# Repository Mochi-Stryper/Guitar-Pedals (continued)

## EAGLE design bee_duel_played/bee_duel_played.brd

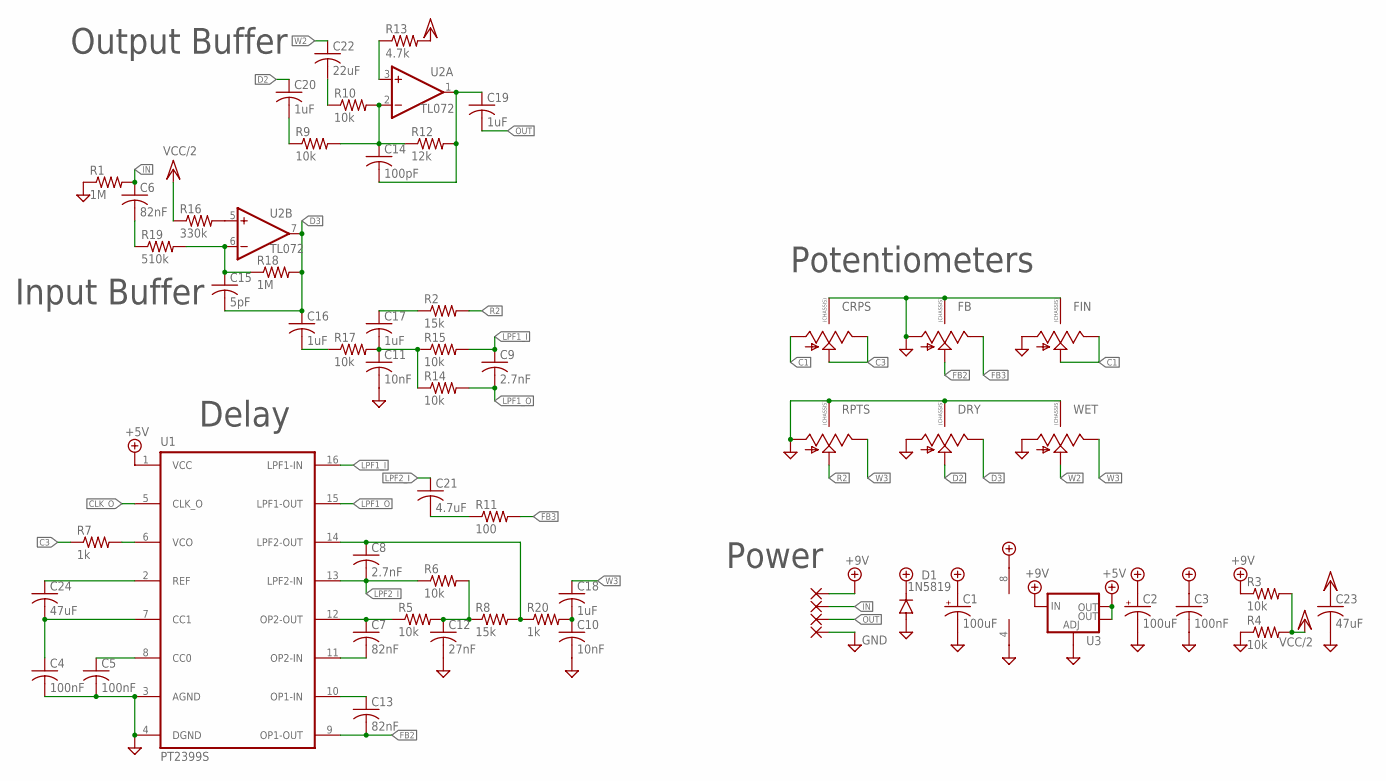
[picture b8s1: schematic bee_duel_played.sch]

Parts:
C1, C2: 100uF; CPOL-RADIAL-2.5MM-6.5MM
C3, C4, C5: 100nF; C0603
C6, C7, C13: 82nF; C0603
C8, C9: 2.7nF; C0603
C10, C11: 10nF; C0603
C12: 27nF; C0603
C14: 100pF; C0603
C15: 5pF; C0603
C16, C17, C18, C19, C20: 1uF; C0603
C21: 4.7uF; C0805
C22: 22uF; C1210
C23, C24: 47uF; C1210
CRPS: 9MM_SNAP-IN_POT_CHASSIS; 9MM_SNAP-IN_POT
D1: 1N5819; SOD123
DRY: 9MM_SNAP-IN_POT_CHASSIS; 9MM_SNAP-IN_POT
FB: 9MM_SNAP-IN_POT_CHASSIS; 9MM_SNAP-IN_POT
FIN: 9MM_SNAP-IN_POT_CHASSIS; 9MM_SNAP-IN_POT
PAD1, PAD2, PAD3, PAD4: 1,6/0,8
R1, R18: 1M; R0603
R2, R8: 15k; R0603
R3, R4, R5, R6, R9, R10, R14, R15, R17: 10k; R0603
R7, R20: 1k; R0603
R11: 100; R0603
R12: 12k; R0603
R13: 4.7k; R0603
R16: 330k; R0603
R19: 510k; R0603
RPTS: 9MM_SNAP-IN_POT_CHASSIS; 9MM_SNAP-IN_POT
U1: PT2399S; SO16W
U2: TL072; TSSOP-8
U3: V_REG_LM1117SOT223; SOT223
WET: 9MM_SNAP-IN_POT_CHASSIS; 9MM_SNAP-IN_POT

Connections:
+5V: C2.1 (+), C3.1, U1.1 (VCC), U3.2 (OUT), U3.4 (OUT)
+9V: C1.1 (+), D1.C, PAD1.1, R3.1, U2.8 (V+), U3.3 (IN)
C1: CRPS.1 (A), FIN.2 (S), FIN.3 (E)
C3: CRPS.2 (S), CRPS.3 (E), R7.1
CLK_O: U1.5 (CLK_O)
D2: C20.1, DRY.2 (S)
D3: C15.2, C16.1, DRY.3 (E), R18.2, U2.7 (OUT)
FB2: C13.2, FB.2 (S), U1.9 (OP1-OUT)
FB3: FB.3 (E), R11.2
GND: C1.2 (-), C2.2 (-), C3.2, C4.2, C5.2, C10.2, C11.2, C12.2, C23.2, CRPS.CHASSIS1, CRPS.CHASSIS2, D1.A, DRY.1 (A), DRY.CHASSIS1, DRY.CHASSIS2, FB.1 (A), FB.CHASSIS1, FB.CHASSIS2, FIN.1 (A), FIN.CHASSIS1, FIN.CHASSIS2, PAD4.1, R1.1, R4.1, RPTS.1 (A), RPTS.CHASSIS1, RPTS.CHASSIS2, U1.3 (AGND), U1.4 (DGND), U2.4 (V-), U3.1 (ADJ), WET.1 (A), WET.CHASSIS1, WET.CHASSIS2
IN: C6.1, PAD2.1, R1.2
LPF1_I: C9.1, R15.2, U1.16 (LPF1-IN)
LPF1_O: C9.2, R14.2, U1.15 (LPF1-OUT)
LPF2_I: C8.2, C21.1, R6.1, U1.13 (LPF2-IN)
LPF2_O: C8.1, R8.2, R20.1, U1.14 (LPF2-OUT)
unnamed: R16.2, U2.5 (+IN)
unnamed: C6.2, R19.1
unnamed: C15.1, R18.1, R19.2, U2.6 (-IN)
unnamed: C16.2, R17.1
unnamed: C11.1, C17.2, R14.1, R15.1, R17.2
unnamed: C5.1, U1.8 (CC0)
unnamed: C17.1, R2.1
unnamed: C13.1, U1.10 (OP1-IN)
unnamed: C7.2, U1.11 (OP2-IN)
unnamed: C7.1, R5.1, U1.12 (OP2-OUT)
unnamed: C12.1, R5.2, R6.2, R8.1
unnamed: C10.1, C18.2, R20.2
unnamed: C22.2, R10.1
unnamed: C21.2, R11.1
unnamed: C14.1, R9.2, R10.2, R12.1, U2.2 (-IN)
unnamed: R13.1, U2.3 (+IN)
unnamed: C4.1, C24.2, U1.7 (CC1)
unnamed: C24.1, U1.2 (REF)
unnamed: R7.2, U1.6 (VCO)
unnamed: C14.2, C19.1, R12.2, U2.1 (OUT)
unnamed: C20.2, R9.1
OUT: C19.2, PAD3.1
R2: R2.2, RPTS.2 (S)
VCC/2: C23.1, R3.2, R4.2, R13.2, R16.1
W2: C22.1, WET.2 (S)
W3: C18.1, RPTS.3 (E), WET.3 (E)

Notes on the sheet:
Input Buffer
Output Buffer
Potentiometers
Power
Delay

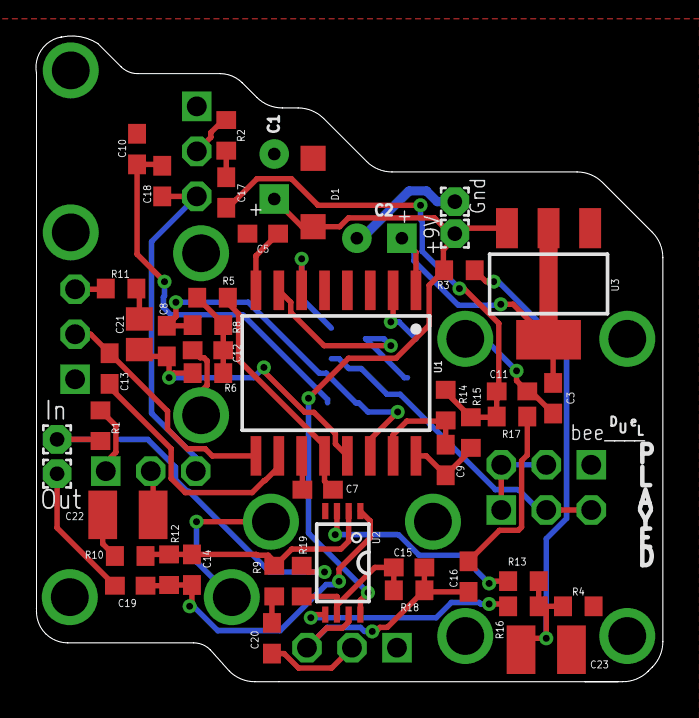
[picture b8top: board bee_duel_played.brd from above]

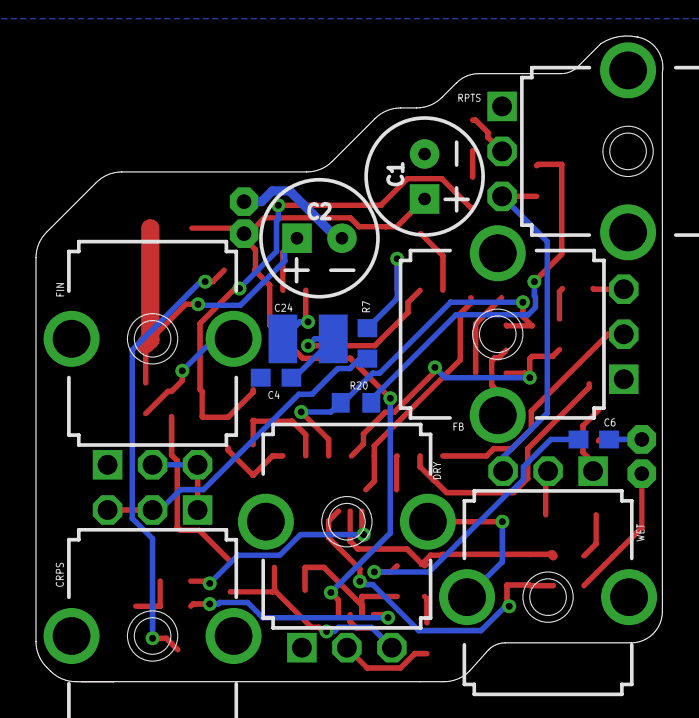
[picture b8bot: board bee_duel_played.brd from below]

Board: 2 copper layers, 34.8 x 35.9 mm, 58 parts (13 on the bottom side), 40 nets.
